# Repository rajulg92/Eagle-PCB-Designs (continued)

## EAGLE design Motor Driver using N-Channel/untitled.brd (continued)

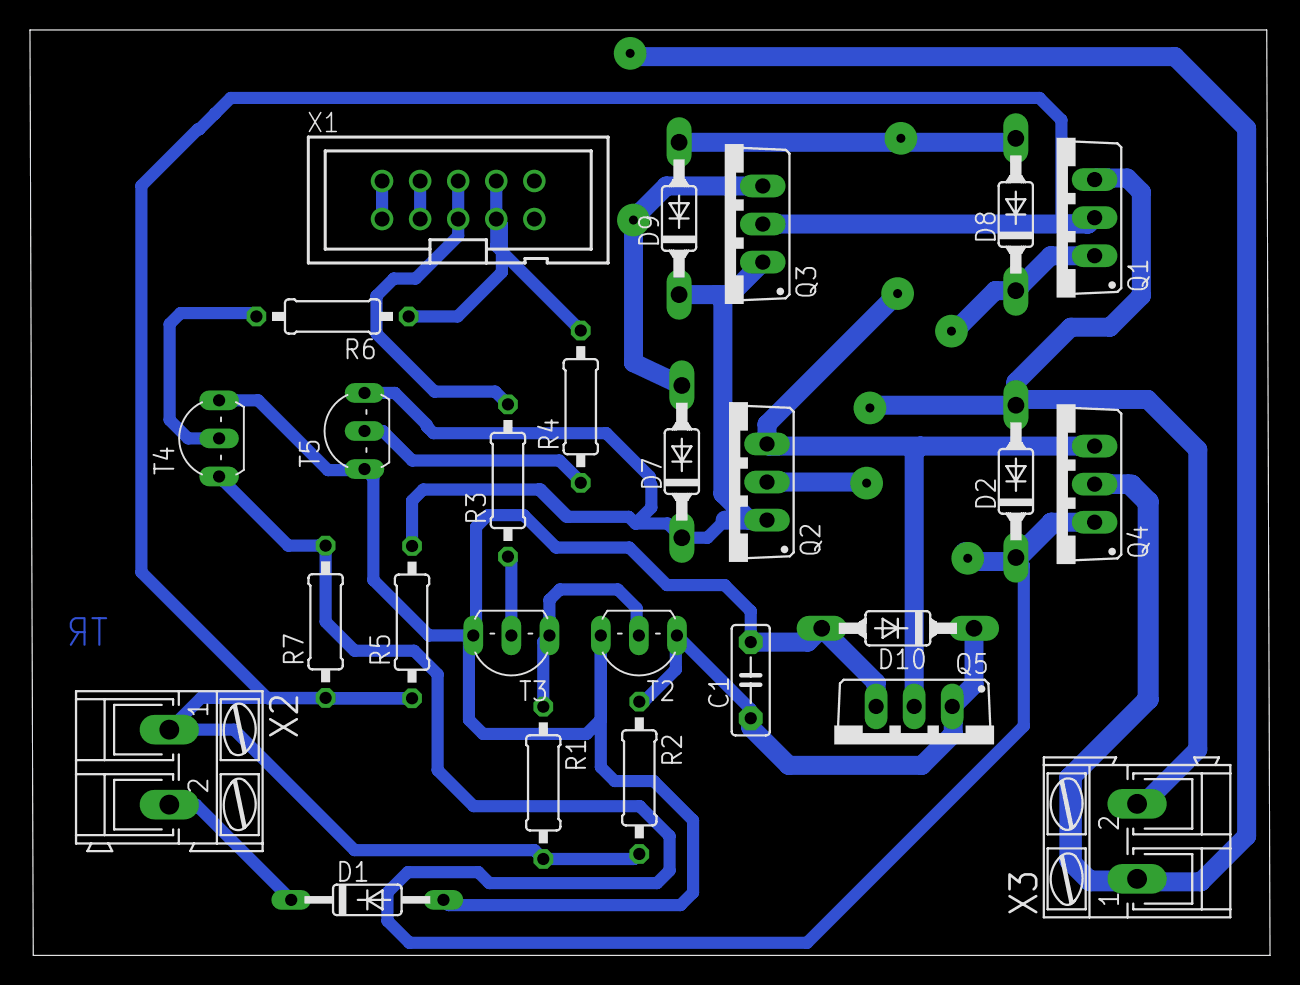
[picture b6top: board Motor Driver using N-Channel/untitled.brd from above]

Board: 2 copper layers, 82.7 x 61.7 mm, 26 parts (0 on the bottom side), 17 nets.

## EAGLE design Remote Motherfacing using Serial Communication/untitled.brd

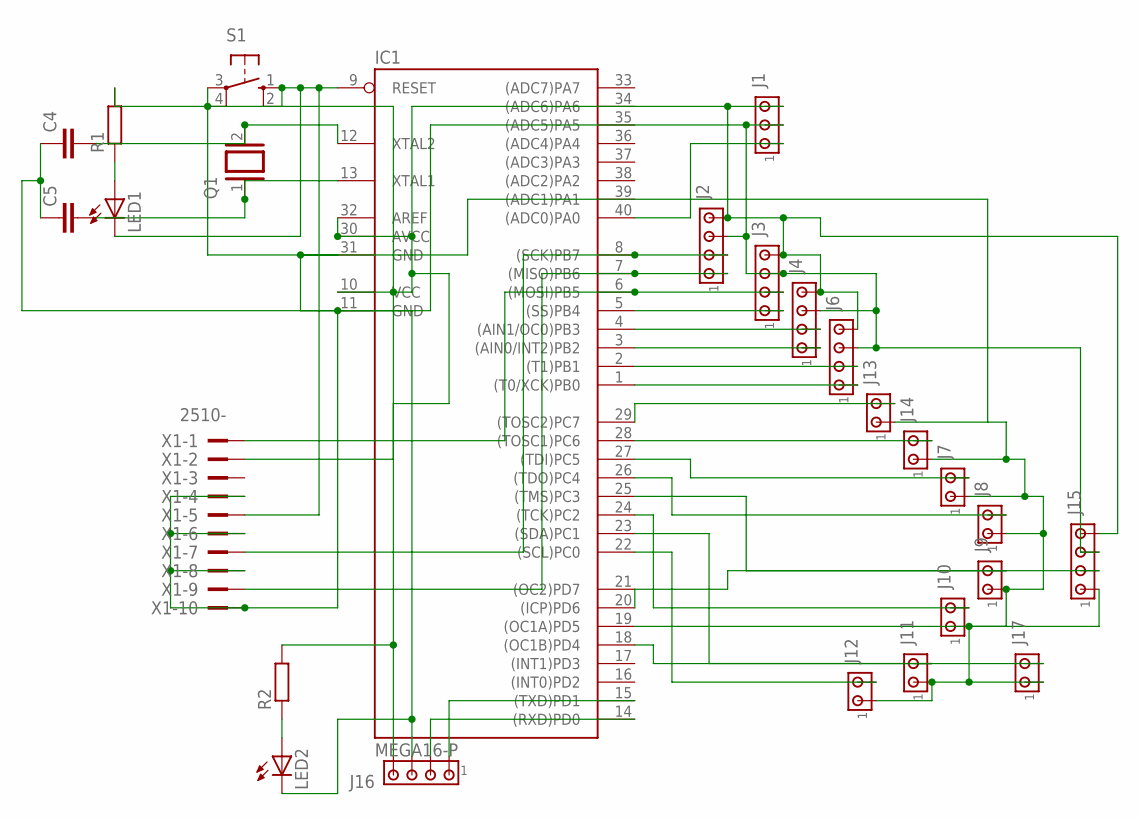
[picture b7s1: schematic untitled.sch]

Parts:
C4, C5: C2.5/2; C2.5-2
IC1: MEGA16-P; DIL40
J1: MTA03-100; 10X03MTA
J2, J3, J4, J6, J15, J16: MTA04-100; 10X04MTA
J7, J8, J9, J10, J11, J12, J13, J14, J17: MTA02-100; 10X02MTA
LED1, LED2: LEDSFH482; SFH482
Q1: XTAL/S; QS
R1, R2: R-EU_0207/10; 0207/10
S1: 10-XX; B3F-10XX
X1: 2510-; PAK100/2500-10

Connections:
unnamed: IC1.29 ((TOSC2)PC7), J13.2
unnamed: IC1.9 (RESET), LED1.K (C), S1.1 (S), S1.2 (S1), X1.5
unnamed: IC1.40 ((ADC0)PA0), J1.1
unnamed: IC1.1 ((T0/XCK)PB0), J6.1
unnamed: IC1.2 ((T1)PB1), J6.2
unnamed: IC1.3 ((AIN0/INT2)PB2), J4.1
unnamed: IC1.4 ((AIN1/OC0)PB3), J4.2
unnamed: IC1.5 ((SS)PB4), J3.1
unnamed: IC1.6 ((MOSI)PB5), J3.2, X1.1
unnamed: IC1.7 ((MISO)PB6), J2.1, X1.9
unnamed: IC1.8 ((SCK)PB7), J2.2, X1.7
unnamed: IC1.10 (VCC), IC1.30 (AVCC), IC1.32 (AREF), J1.3, J2.4, J3.4, J4.4, J6.4, J15.4, J16.4, R1.2, R2.2, X1.2
unnamed: IC1.28 ((TOSC1)PC6), J14.2
unnamed: IC1.27 ((TDI)PC5), J7.2
unnamed: IC1.26 ((TDO)PC4), J8.2
unnamed: IC1.25 ((TMS)PC3), J9.2
unnamed: IC1.24 ((TCK)PC2), J10.2
unnamed: IC1.23 ((SDA)PC1), J11.2
unnamed: IC1.22 ((SCL)PC0), J12.2
unnamed: LED2.A, R2.1
unnamed: IC1.19 ((OC1A)PD5), J15.1
unnamed: IC1.15 ((TXD)PD1), J16.1
unnamed: IC1.20 ((ICP)PD6), J15.2
unnamed: IC1.14 ((RXD)PD0), J16.2
unnamed: LED1.A, R1.1
unnamed: C5.2, IC1.13 (XTAL1), Q1.1
unnamed: C4.2, IC1.12 (XTAL2), Q1.2
unnamed: C4.1, C5.1, IC1.11 (GND), IC1.31 (GND), J1.2, J2.3, J3.3, J4.3, J6.3, J7.1, J8.1, J9.1, J10.1, J11.1, J12.1, J13.1, J14.1, J15.3, J16.3, J17.1, LED2.K (C), S1.3, S1.4 (P1), X1.4, X1.6, X1.8, X1.10
unnamed: IC1.18 ((OC1B)PD4), J17.2

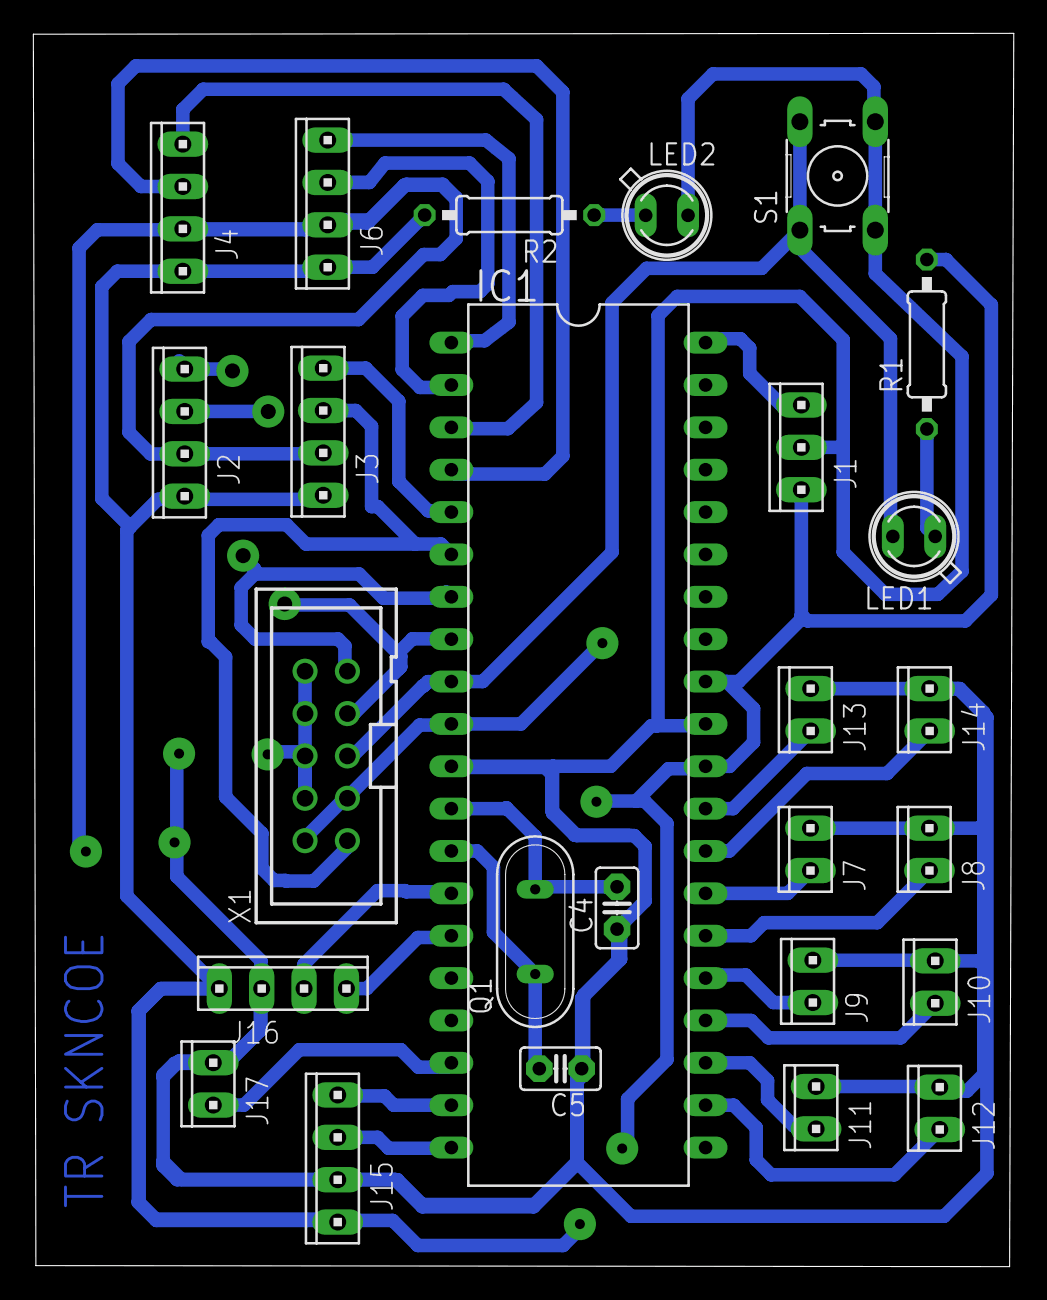
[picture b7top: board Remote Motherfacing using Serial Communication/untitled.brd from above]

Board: 2 copper layers, 58.8 x 73.9 mm, 26 parts (0 on the bottom side), 29 nets.

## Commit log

2018-04-11 Intial Commit
2018-04-11 MS Project PCB Design added with Gerbers
2018-04-12 MS Project PCB Design Added
